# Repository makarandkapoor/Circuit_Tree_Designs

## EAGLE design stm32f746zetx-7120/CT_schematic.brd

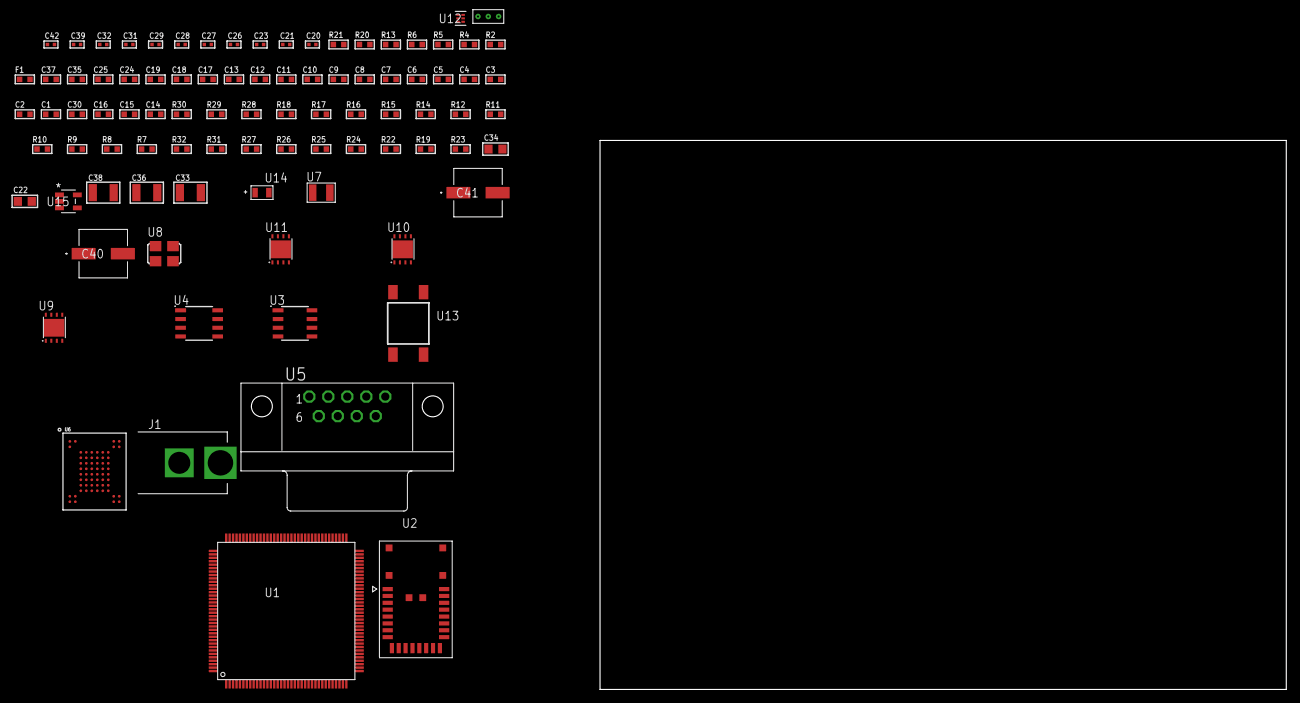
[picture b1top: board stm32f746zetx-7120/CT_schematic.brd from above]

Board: 2 copper layers, 100.0 x 80.0 mm, 90 parts (0 on the bottom side), 58 nets, no tracks yet.

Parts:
C1, C18, C24, C25: 1e-06; C0603
C2, C3, C4, C5, C6, C7, C8, C9, C10, C11, C12, C13, C19: 1e-07; C0603
C14: 4.7e-06; C0603
C15, C16, C30: 2.2e-06; C0603
C17: 1e-08; C0603
C20, C21: 1e-11; C0402
C22, C34: 1e-05; C0805
C23, C31, C32, C42: 1e-08; C0402
C26, C27, C28, C29, C39: 1e-07; C0402
C33, C36, C38: 1e-05; C1210
C35, C37: 8e-07; R0603
C40, C41: 0.0001; EXV-9H
F1: 240.0; L0603
J1: PJ-037B; PJ-037B_PACKAGE
R2, R21: 1000.0; R0603
R4: 4700.0; R0603
R5, R6: 2200.0; R0603
R7, R8, R9, R10, R11, R12, R14, R15, R16, R17, R18, R28, R29: 10000.0; R0603
R13: 120.0; R0603
R19, R22, R24, R25, R27: 100000.0; R0603
R20: 806.0; R0603
R23: 153694.38; R0603
R26, R31: 300000.0; R0603
R30: 82000.0; R0603
R32: 120000.0; R0603
U1: STM32F746ZET6; LQFP144
U2: A2500R24A00GM
U3: AT24C02D-SSHM-T; AT24C02D
U4: MCP2562-E/SN; SOIC-8
U5: 182-009-113R531; 182-009-MALE
U6: mt29f4g08abbdah4; VFBGA-63
U7: ABS07-32.768KHZ-7-T
U8: ASFL1-25MHZ-NCS; ASFL1
U9: LP3878SDX-ADJ/NOPB; WSON-8
U10, U11: LP2951ACSDX/NOPB; WSON-8
U12: TPS3895ADRYR; SON-6
U13: 4-1437565-2; SW_4-1437565-2
U14: Q65110A2395; LGM67K-G1J2-24-Z
U15: nc7sz125m5x; NC7SZ125M5X
U16: Dummy; DUMMY_PACKAGE_199

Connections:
CLK_CRYSTAL_U1_8: C20.1, U1.8, U7.1
CLK_CRYSTAL_U1_9: C21.1, U1.9, U7.2
CLK_U1_23: U1.23, U8.3
GND: C1.2, C2.2, C3.2, C4.2, C5.2, C6.2, C7.2, C8.2, C9.2, C10.2, C11.2, C12.2, C13.2, C14.2, C15.2, C16.2, C17.2, C18.2, C19.2, C20.2, C21.2, C22.2, C23.2, C24.2, C25.2, C26.2, C27.2, C28.2, C29.2, C30.2, C31.2, C32.2, C33.2, C34.2, C35.2, C36.2, C37.2, C38.2, C39.2, C40.2, C41.2, C42.2, J1.2, R2.2, R7.2, R9.2, R11.2, R12.2, R21.2, R24.2, R27.2, R30.2, R32.2, U1.16, U1.31, U1.38, U1.51, U1.61, U1.83, U1.94, U1.107, U1.120, U1.130, U2.8, U2.17, U3.4, U4.2, U4.8, U5.5, U6.C5, U6.F7, U6.K3, U6.K8, U8.2, U9.3, U9.PAD, U10.3, U10.4, U10.PAD, U11.3, U11.4, U11.PAD, U12.2, U14.C, U15.1, U15.3, U16.1
NET_U1_25: R4.1, U1.25, U15.4
NET_U1_33: C17.1, C18.1, F1.1, U1.32, U1.33
NET_U1_71: C15.1, U1.71
NET_U1_106: C16.1, U1.106
NET_U1_136: R5.1, U1.136, U3.6
NET_U1_137: R6.1, U1.137, U3.5
NET_U1_138: R7.1, U1.138
NET_U1_142: U13.3, U13.4
NET_U1_143: R8.1, U1.143
NET_U3_1: R10.1, U3.1
NET_U3_2: R11.1, U3.2
NET_U3_3: R12.1, U3.3
NET_U3_7: R9.1, U3.7
NET_U4_6: R13.2, U4.6
NET_U5_2: R13.2, U4.6, U5.2
NET_U5_3: R13.1, U4.7, U5.3
NET_U6_C3: R18.1, U6.C3
NET_U9_1: C32.1, U9.1
NET_U9_6: R20.2, R21.1, U9.6
NET_U9_8: R19.1, U9.8
NET_U10_5: R22.1, U10.5
NET_U10_7: R23.2, R24.1, U10.7
NET_U11_5: R25.1, U11.5
NET_U11_7: R26.2, R27.1, U11.7
NET_U12_1: R29.1, R30.1, U12.1
NET_U12_3: R31.2, R32.1, U12.3
NET_U12_4: R28.1, U12.4, U15.2
NET_U13_1: R2.1, U13.1, U13.2
PROC_CAN1_RX: U1.103, U4.4
PROC_CAN1_TX: U1.104, U4.1
PROC_FMC_A16: U1.80, U6.D5
PROC_FMC_A17: U1.81, U6.C4
PROC_FMC_D0: U1.85, U6.H4
PROC_FMC_D1: U1.86, U6.J4
PROC_FMC_D2: U1.114, U6.K4
PROC_FMC_D3: U1.115, U6.K5
PROC_FMC_D4: U1.58, U6.K6
PROC_FMC_D5: U1.59, U6.J7
PROC_FMC_D6: U1.60, U6.K7
PROC_FMC_D7: U1.63, U6.J8
PROC_FMC_INT: R14.1, U1.92, U6.C8
PROC_FMC_NCE: R15.1, U1.124, U6.C6
PROC_FMC_NOE: R17.1, U1.118, U6.D4
PROC_FMC_NWE: R16.1, U1.119, U6.C7
PROC_SPI1_MISO: U1.42, U2.10
PROC_SPI1_MOSI: U1.43, U2.11
PROC_SPI1_NSS: U1.40, U2.12
PROC_SPI1_SCK: U1.41, U2.9
PROC_TIM1_CH2: U1.64, U16.2
PROC_TIM1_CH4: U1.67, U16.3
VCC_S1_14V9: C33.1, C35.1, C37.1, C40.1, C41.1, J1.1, R19.2, U9.4, U10.8, U11.8
VCC_TIER1_1V8: C1.1, C2.1, C3.1, C4.1, C5.1, C6.1, C7.1, C8.1, C9.1, C10.1, C11.1, C12.1, C13.1, C14.1, C22.1, C23.1, C25.1, C26.1, C27.1, C28.1, C29.1, C30.1, C34.1, C39.1, C42.1, F1.2, R4.2, R5.2, R6.2, R8.2, R10.2, R14.2, R15.2, R16.2, R17.2, R18.2, R20.1, R28.2, R29.2, R31.1, U1.6, U1.17, U1.30, U1.39, U1.52, U1.62, U1.72, U1.84, U1.108, U1.121, U1.131, U1.144, U2.18, U3.8, U4.5, U6.D3, U6.G4, U6.H8, U6.J6, U9.5, U12.6, U15.5
VCC_TIER1_3V3: C19.1, C31.1, C36.1, R22.2, R23.1, U1.95, U8.4, U10.1
VCC_TIER1_5V0: C24.1, C38.1, R25.2, R26.1, U4.3, U11.1

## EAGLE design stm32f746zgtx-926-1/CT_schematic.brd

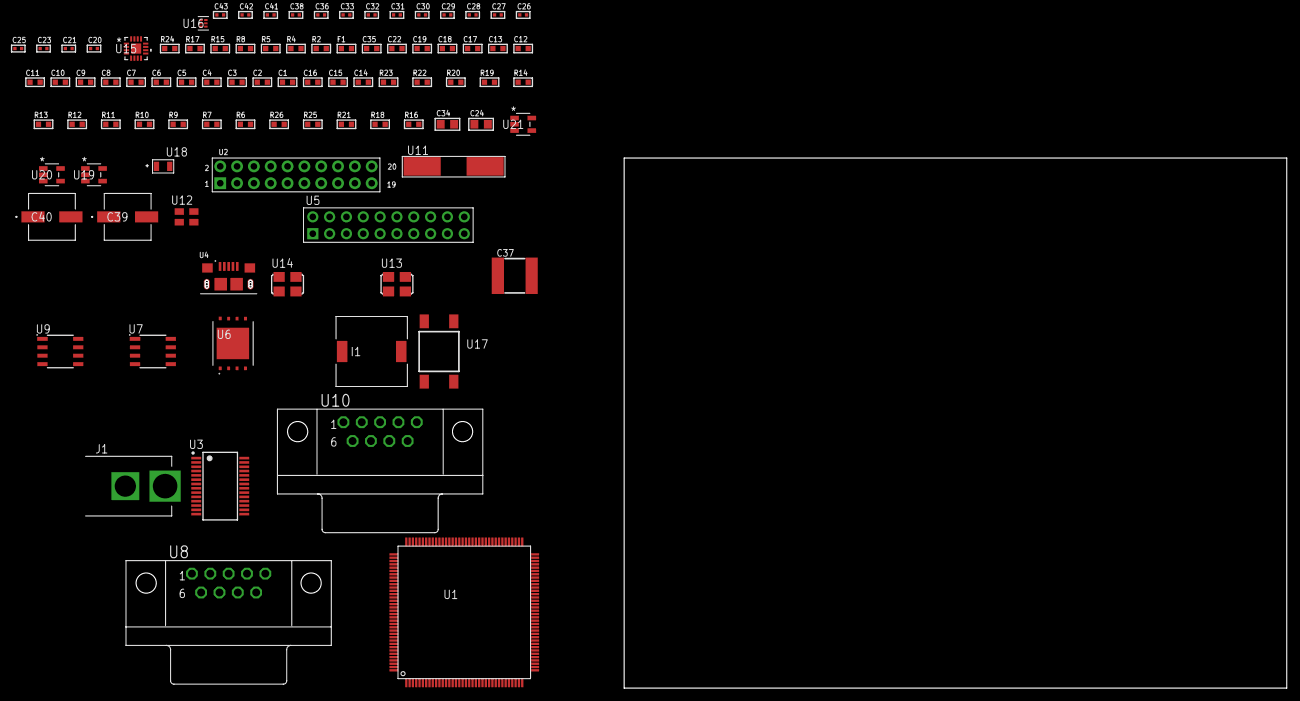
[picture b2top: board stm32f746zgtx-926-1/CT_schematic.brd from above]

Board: 2 copper layers, 91 parts (0 on the bottom side), 67 nets, no tracks yet.

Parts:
C1, C18, C22, C35: 1e-06; C0603
C2, C3, C4, C5, C6, C7, C8, C9, C10, C11, C12, C13, C19: 1e-07; C0603
C14: 4.7e-06; C0603
C15, C16: 2.2e-06; C0603
C17: 1e-08; C0603
C20, C21: 1e-11; C0402
C23, C25, C26, C27, C29, C30, C36, C38: 1e-07; C0402
C24: 4.7e-06; C0805
C28, C31, C32, C33, C41, C42, C43: 1e-08; C0402
C34: 1e-05; C0805
C37: 6.8e-05; 2220
C39, C40: 0.0001; EXV-9H
F1: 240.0; L0603
I1: 3.8e-06; DR1040
J1: PJ-037B; PJ-037B_PACKAGE
R2: 1000.0; R0603
R4, R5, R8: 4700.0; R0603
R6, R7, R9, R10, R11, R12, R13, R14, R22, R23: 10000.0; R0603
R15, R17: 120.0; R0603
R16: 100000.0; R0603
R18: 470000.0; R0603
R19: 20000.0; R0603
R20: 91000.0; R0603
R21: 300000.0; R0603
R24: 9100.0; R0603
R25: 680000.0; R0603
R26: 120000.0; R0603
U1: STM32F746ZGT6; LQFP144
U2: arducam_ov2640; ARDUCAM
U3: FT232RL-REEL; SSOP-28
U4: 10118193-0001LF; FCI_10118193-0001LF
U5: TST-110-05-T-D-RA
U6: S25FL128SDPNFI001; WNG008
U7, U9: SN65HVD230D; SOIC-8
U8, U10: 182-009-113R531; 182-009-MALE
U11: ABLS-25.000MHZ-B2F-T
U12: ASEK-32.768KHz-ECST; ASEK
U13: ASFL1-12MHZ-NCS; ASFL1
U14: ASFL1-25MHZ-NCS; ASFL1
U15: LTC3601EUD#PBF; QFN-16_EP
U16: TPS3895ADRYR; SON-6
U17: 4-1437565-2; SW_4-1437565-2
U18: Q65110A2395; LGM67K-G1J2-24-Z
U19, U20, U21: nc7sz125m5x; NC7SZ125M5X

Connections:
CLK_CRYSTAL_U1_23: C20.1, U1.23, U11.1
CLK_CRYSTAL_U1_24: C21.1, U1.24, U11.2
CLK_U1_8: U1.8, U12.3
CLK_U2_8: U2.8, U14.3
CLK_U3_27: U3.27, U13.3
GND: C1.2, C2.2, C3.2, C4.2, C5.2, C6.2, C7.2, C8.2, C9.2, C10.2, C11.2, C12.2, C13.2, C14.2, C15.2, C16.2, C17.2, C18.2, C19.2, C20.2, C21.2, C22.2, C23.2, C24.2, C25.2, C26.2, C27.2, C28.2, C29.2, C30.2, C31.2, C32.2, C33.2, C34.2, C35.2, C37.1, C37.2, C38.2, C39.2, C40.2, C41.2, C42.2, C43.2, J1.2, R2.2, R6.2, R10.2, R16.2, R18.2, R19.2, R21.2, R24.2, R26.2, U1.16, U1.31, U1.38, U1.51, U1.61, U1.83, U1.94, U1.107, U1.120, U1.130, U2.2, U2.20, U3.7, U3.18, U3.21, U3.25, U3.26, U4.5, U4.6, U4.7, U4.8, U4.9, U5.4, U5.6, U5.8, U5.10, U5.12, U5.14, U5.16, U5.18, U5.20, U6.4, U6.PAD, U7.2, U8.5, U9.2, U10.5, U12.2, U13.2, U14.2, U15.1, U15.9, U15.17, U16.2, U18.C, U19.2, U19.3, U20.1, U20.3, U21.1, U21.3
NET_U1_25: R4.1, U1.25, U20.4
NET_U1_33: C17.1, C18.1, F1.1, U1.32, U1.33
NET_U1_71: C15.1, U1.71
NET_U1_106: C16.1, U1.106
NET_U1_138: R6.1, U1.138
NET_U1_142: U17.3, U17.4
NET_U1_143: R7.1, U1.143
NET_U2_19: R5.1, U2.19, U21.4
NET_U3_14: R9.1, U3.14
NET_U3_17: C25.1, U3.17
NET_U3_19: R10.1, U3.19
NET_U4_1: R8.1, U4.1
NET_U4_2: U3.16, U4.2
NET_U4_3: U3.15, U4.3
NET_U6_3: R12.1, U6.3
NET_U6_7: R14.1, U6.7
NET_U7_6: R15.2, U7.6
NET_U7_8: R16.1, U7.8
NET_U8_2: R15.2, U7.6, U8.2
NET_U8_3: R15.1, U7.7, U8.3
NET_U9_6: R17.2, U9.6
NET_U9_8: R18.1, U9.8
NET_U10_2: R17.2, U9.6, U10.2
NET_U10_3: R17.1, U9.7, U10.3
NET_U15_3: C36.2, I1.1, U15.3, U15.4
NET_U15_6: C36.1, U15.6
NET_U15_7: C35.1, U15.7, U15.12
NET_U15_10: R21.1, U15.10
NET_U15_11: R19.1, R20.1, U15.11
NET_U15_ATNET_3: I1.2, R20.2
NET_U16_1: R23.1, R24.1, U16.1
NET_U16_3: R25.2, R26.1, U16.3
NET_U16_4: R22.1, U16.4, U19.4, U20.2, U21.2
NET_U17_1: R2.1, U17.1, U17.2
PROC_CAN1_RX: U1.103, U7.4
PROC_CAN1_TX: U1.104, U7.1
PROC_CAN2_RX: U1.73, U9.4
PROC_CAN2_TX: U1.74, U9.1
PROC_DCMI_D0: U1.96, U2.18
PROC_DCMI_D1: U1.97, U2.17
PROC_DCMI_D2: U1.98, U2.16
PROC_DCMI_D3: U1.99, U2.15
PROC_DCMI_D4: U1.3, U2.14
PROC_DCMI_D5: U1.117, U2.13
PROC_DCMI_D6: U1.4, U2.12
PROC_DCMI_D7: U1.5, U2.11
PROC_DCMI_D8: U1.111, U2.10
PROC_DCMI_D9: U1.113, U2.9
PROC_DCMI_HSYNC: U1.40, U2.6
PROC_DCMI_PIXCLK: U1.42, U2.7
PROC_DCMI_VSYNC: U1.124, U2.5
PROC_SPI2_MISO: U1.28, U6.2
PROC_SPI2_MOSI: U1.27, U6.5
PROC_SPI2_NSS: R13.1, U1.134, U6.1
PROC_SPI2_SCK: U1.69, U6.6
PROC_SYS_JTCK_SWCLK: U1.109, U5.9
PROC_SYS_JTDO_SWO: U1.133, U5.13
PROC_SYS_JTMS_SWDIO: U1.105, U5.7
RST_OUT_U5_SRESET_B: R11.1, U5.15, U19.1
VCC_S1_9V0: C34.1, C39.1, C40.1, J1.1, U15.15, U15.16
VCC_TIER1_3V3: C1.1, C2.1, C3.1, C4.1, C5.1, C6.1, C7.1, C8.1, C9.1, C10.1, C11.1, C12.1, C13.1, C14.1, C19.1, C22.1, C23.1, C24.1, C26.1, C27.1, C28.1, C29.1, C30.1, C31.1, C32.1, C33.1, C37.2, C38.1, C41.1, C42.1, C43.1, F1.2, I1.2, R4.2, R5.2, R7.2, R9.2, R11.2, R12.2, R13.2, R14.2, R20.2, R22.2, R23.2, R25.1, U1.6, U1.17, U1.30, U1.39, U1.52, U1.62, U1.72, U1.84, U1.95, U1.108, U1.121, U1.131, U1.144, U2.1, U3.4, U3.20, U5.1, U6.8, U7.3, U9.3, U12.4, U13.4, U14.4, U15.8, U16.6, U19.5, U20.5, U21.5

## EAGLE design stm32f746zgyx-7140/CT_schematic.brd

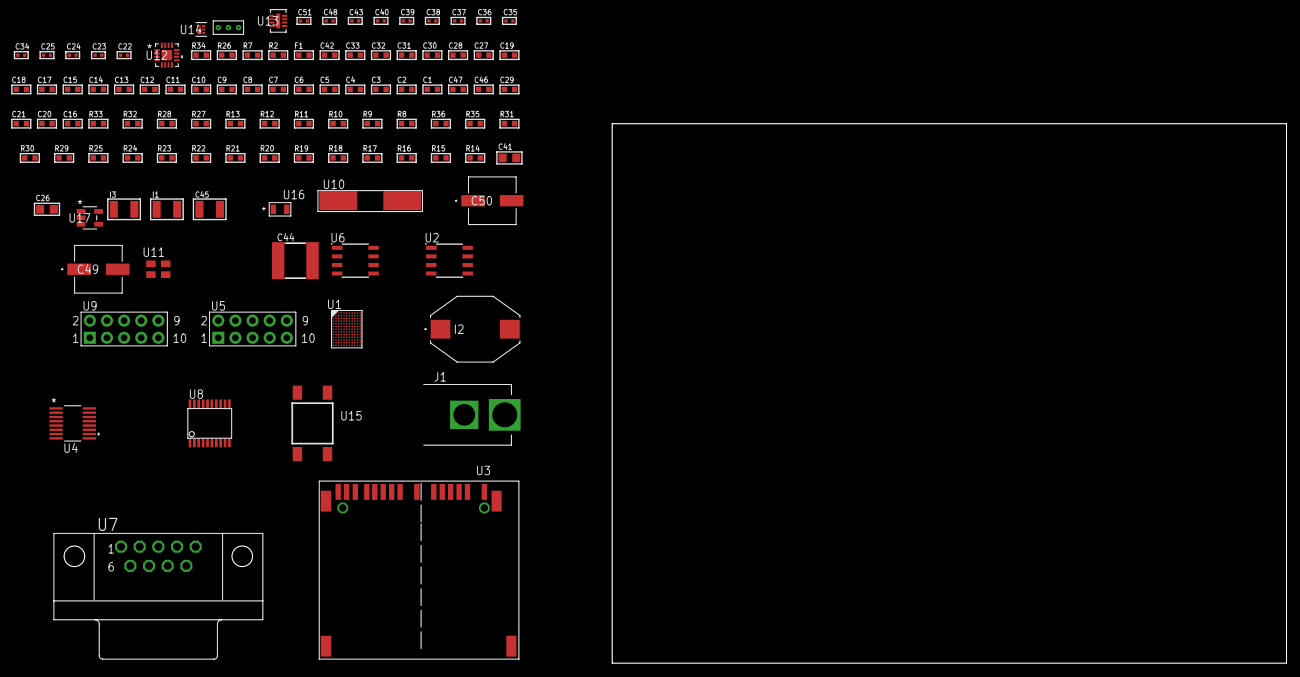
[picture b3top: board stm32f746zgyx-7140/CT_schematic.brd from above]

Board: 2 copper layers, 100.0 x 80.0 mm, 105 parts (0 on the bottom side), 81 nets, no tracks yet.

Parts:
C1, C18, C27, C28, C30, C31, C32, C33, C42: 1e-06; C0603
C2, C3, C4, C5, C6, C7, C8, C9, C10, C11, C12, C13, C14, C15, C19: 1e-07; C0603
C16: 4.7e-06; C0603
C17: 1e-08; C0603
C20, C21, C46: 2.2e-06; C0603
C22, C23: 1e-11; C0402
C24, C40, C51: 1e-08; C0402
C25, C34, C35, C36, C37, C38, C39, C43, C48: 1e-07; C0402
C26, C41: 1e-05; C0805
C29, C47: 2.2e-07; C0603
C44: 6.8e-05; 2220
C45: 1e-05; C1210
C49, C50: 0.0001; EXV-9H
F1: 240.0; L0603
I1, I3: 1e-05; L1210
I2: 1.5e-06; IND_PM3316
J1: PJ-037B; PJ-037B_PACKAGE
R2: 1000.0; R0603
R7: 4700.0; R0603
R8, R9, R10, R11, R12, R13, R32, R33: 10000.0; R0603
R14, R15, R16, R17, R18, R19, R20, R21, R22, R23, R24, R25, R30: 100000.0; R0603
R26: 120.0; R0603
R27: 20000.0; R0603
R28: 91000.0; R0603
R29: 300000.0; R0603
R31: 560000.0; R0603
R34: 9100.0; R0603
R35: 680000.0; R0603
R36: 120000.0; R0603
U1: STM32F746ZGY6; WLCSP143
U2: AT25128B-SSHL-T; SOIC-8
U3: 10100565
U4: LTC2804CGN-1#PBF; SSOP-16
U5, U9: HTSS-105-01-G-D
U6: MCP2562-E/SN; SOIC-8
U7: 182-009-113R531; 182-009-MALE
U8: SP3203ECY-L/TR; TSSOP20-I
U10: ABLS-25.000MHZ-B2F-T
U11: ASEK-32.768KHz-ECST; ASEK
U12: LTC3601EUD#PBF; QFN-16_EP
U13: LT3494AEDDB#TRMPBF; DFN-8_DDB
U14: TPS3895ADRYR; SON-6
U15: 4-1437565-2; SW_4-1437565-2
U16: Q65110A2395; LGM67K-G1J2-24-Z
U17: nc7sz125m5x; NC7SZ125M5X
U18: Dummy; DUMMY_PACKAGE_222

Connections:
CLK_CRYSTAL_U1_H10: C22.1, U1.H10, U10.1
CLK_CRYSTAL_U1_J11: C23.1, U1.J11, U10.2
CLK_U1_D11: U1.D11, U11.3
GND: C1.2, C2.2, C3.2, C4.2, C5.2, C6.2, C7.2, C8.2, C9.2, C10.2, C11.2, C12.2, C13.2, C14.2, C15.2, C16.2, C17.2, C18.2, C19.2, C20.2, C21.2, C22.2, C23.2, C24.2, C25.2, C26.2, C27.2, C28.2, C30.2, C31.2, C32.2, C33.2, C34.2, C35.2, C38.2, C39.2, C40.2, C41.2, C42.2, C44.1, C44.2, C45.2, C46.2, C47.2, C48.2, C49.2, C50.2, C51.2, J1.2, R2.2, R8.2, R10.2, R27.2, R29.2, R34.2, R36.2, U1.D2, U1.E7, U1.F5, U1.H2, U1.H3, U1.H7, U1.K10, U2.4, U3.6, U3.10, U3.12, U3.16, U3.17, U3.20, U3.21, U4.8, U5.9, U6.2, U6.8, U7.5, U8.18, U9.9, U11.2, U12.1, U12.9, U12.17, U13.2, U13.9, U14.2, U16.C, U17.1, U17.3, U18.1
NET_U1_A11: R9.1, U1.A11
NET_U1_C9: R8.1, U1.C9
NET_U1_D1: C21.1, U1.D1
NET_U1_H9: R7.1, U1.H9, U17.4
NET_U1_L10: C17.1, C18.1, F1.1, U1.L10, U1.L11
NET_U1_N2: C20.1, U1.N2
NET_U1_N10: U15.3, U15.4
NET_U1_N11: R10.1, U1.N11
NET_U2_3: R11.1, U2.3
NET_U2_7: R13.1, U2.7
NET_U3_1: R16.1, U3.1
NET_U3_2: R15.1, U3.2
NET_U3_18: U3.18, U3.19
NET_U4_6: C27.1, U4.6
NET_U4_7: C29.1, I1.2, U4.7
NET_U4_9: C28.1, U4.9
NET_U4_10: C29.2, U4.10
NET_U4_11: R25.1, U4.11
NET_U5_3: U4.1, U5.3
NET_U5_4: U4.2, U5.4
NET_U5_5: U4.3, U5.5
NET_U5_6: U4.4, U5.6
NET_U6_6: R26.2, U6.6
NET_U7_2: R26.2, U6.6, U7.2
NET_U7_3: R26.1, U6.7, U7.3
NET_U8_1: C36.1, U8.1
NET_U8_2: C38.1, U8.2
NET_U8_3: C36.2, U8.3
NET_U8_4: C37.1, U8.4
NET_U8_5: C37.2, U8.5
NET_U8_6: C39.1, U8.6
NET_U9_3: U8.14, U9.3
NET_U9_4: U8.13, U9.4
NET_U9_5: U8.17, U9.5
NET_U9_6: U8.16, U9.6
NET_U12_3: C43.2, I2.1, U12.3, U12.4
NET_U12_6: C43.1, U12.6
NET_U12_7: C42.1, U12.7, U12.12
NET_U12_10: R29.1, U12.10
NET_U12_11: R27.1, R28.1, U12.11
NET_U12_ATNET_3: I2.2, R28.2
NET_U13_1: I3.1, U13.1
NET_U13_5: R30.1, U13.5
NET_U13_6: R31.1, U13.6
NET_U13_8: C47.1, U13.8
NET_U14_1: R33.1, R34.1, U14.1
NET_U14_3: R35.2, R36.1, U14.3
NET_U14_4: R32.1, U14.4, U17.2
NET_U15_1: R2.1, U15.1, U15.2
PROC_ADC1_IN3: U1.M11, U18.2
PROC_ADC1_IN5: U1.M9, U18.3
PROC_CAN1_RX: U1.B3, U6.4
PROC_CAN1_TX: U1.C4, U6.1
PROC_SDMMC1_CK: R14.1, U1.C3, U3.8
PROC_SDMMC1_D0: R17.1, U1.E4, U3.4
PROC_SDMMC1_D1: R18.1, U1.E3, U3.3
PROC_SDMMC1_D2: R19.1, U1.A2, U3.15
PROC_SDMMC1_D3: R20.1, U1.B2, U3.14
PROC_SDMMC1_D4: R21.1, U1.A9, U3.13
PROC_SDMMC1_D5: R22.1, U1.B9, U3.11
PROC_SDMMC1_D6: R23.1, U1.F2, U3.7
PROC_SDMMC1_D7: R24.1, U1.F3, U3.5
PROC_SPI1_MISO: U1.C7, U2.2
PROC_SPI1_MOSI: U1.C8, U2.5
PROC_SPI1_NSS: R12.1, U1.M10, U2.1
PROC_SPI1_SCK: U1.B7, U2.6
PROC_UART4_CTS: U1.N8, U4.13
PROC_UART4_RTS: U1.C2, U4.15
PROC_UART4_RX: U1.K8, U4.16
PROC_UART4_TX: U1.K9, U4.14
PROC_UART7_CTS: U1.G8, U8.8
PROC_UART7_RTS: U1.H11, U8.10
PROC_UART7_RX: U1.G10, U8.11
PROC_UART7_TX: U1.F7, U8.7
VCC_S1_4V6: C41.1, C45.1, C49.1, C50.1, I3.2, J1.1, R30.2, U12.15, U12.16, U13.3, U13.4
VCC_TIER1_3V3: C1.1, C2.1, C3.1, C4.1, C5.1, C6.1, C7.1, C8.1, C9.1, C10.1, C11.1, C12.1, C13.1, C14.1, C15.1, C16.1, C19.1, C24.1, C25.1, C26.1, C30.1, C31.1, C33.1, C34.1, C35.1, C40.1, C44.2, C48.1, C51.1, F1.2, I1.1, I2.2, R7.2, R9.2, R11.2, R12.2, R13.2, R14.2, R15.2, R16.2, R17.2, R18.2, R19.2, R20.2, R21.2, R22.2, R23.2, R24.2, R25.2, R28.2, R32.2, R33.2, R35.1, U1.A1, U1.C1, U1.C5, U1.C11, U1.D7, U1.E6, U1.E10, U1.G1, U1.G7, U1.J5, U1.J6, U1.J7, U1.J8, U1.L1, U2.8, U3.9, U4.5, U4.12, U6.5, U8.12, U8.19, U11.4, U12.8, U14.6, U17.5
VCC_TIER1_5V0: C32.1, C46.1, R31.2, U6.3, U13.7

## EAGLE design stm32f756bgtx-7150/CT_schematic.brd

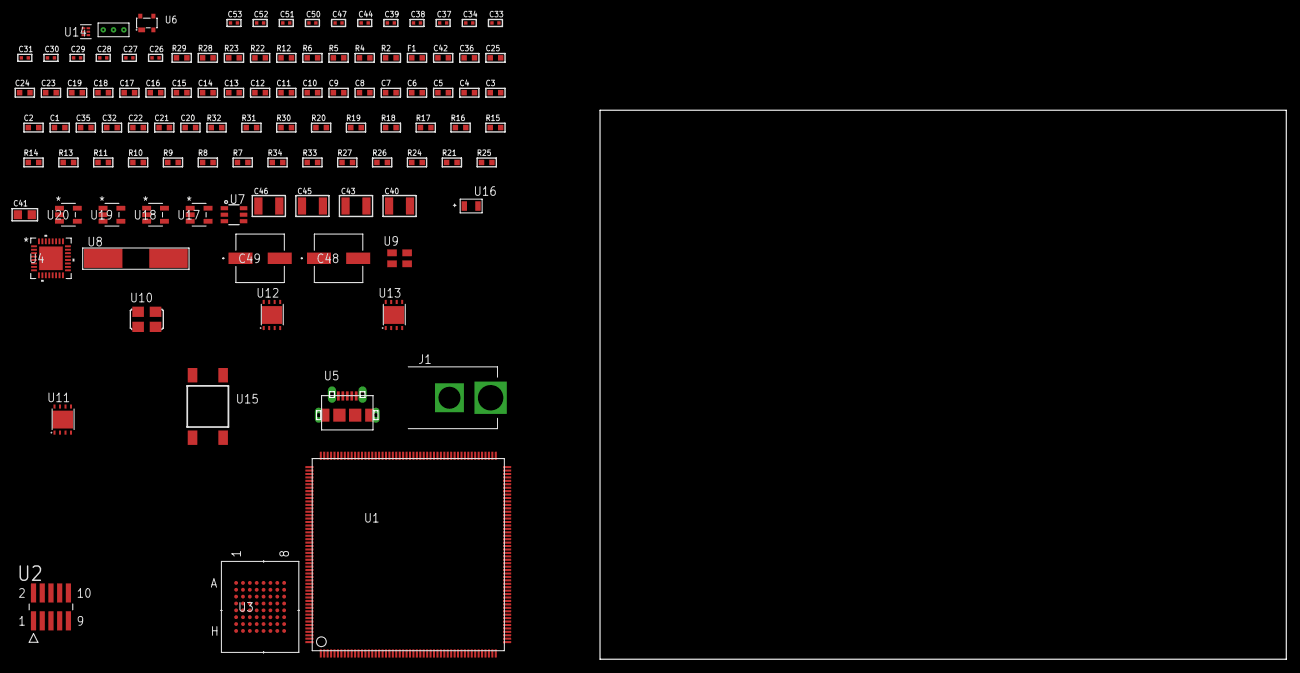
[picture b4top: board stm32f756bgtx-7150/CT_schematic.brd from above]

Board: 2 copper layers, 108 parts (0 on the bottom side), 105 nets, no tracks yet.

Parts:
C1, C24, C36: 1e-06; C0603
C2, C3, C4, C5, C6, C7, C8, C9, C10, C11, C12, C13, C14, C15, C16, C17, C18, C19, C25: 1e-07; C0603
C20: 4.7e-06; C0603
C21, C22, C32, C35: 2.2e-06; C0603
C23: 1e-08; C0603
C26, C27: 1e-11; C0402
C28, C31, C33, C34, C47: 1e-07; C0402
C29, C30, C37, C38, C39, C44, C50, C51, C52, C53: 1e-08; C0402
C40, C43, C45, C46: 1e-05; C1210
C41: 1e-05; C0805
C42: 8e-07; R0603
C48, C49: 0.0001; EXV-9H
F1: 240.0; L0603
J1: PJ-037B; PJ-037B_PACKAGE
R2, R23, R29: 1000.0; R0603
R4, R5, R6: 4700.0; R0603
R7, R8, R9, R10, R11, R13, R14, R15, R16, R17, R19, R20, R30, R31: 10000.0; R0603
R12: 5.0; R0603
R18: 47000.0; R0603
R21, R24, R26, R27: 100000.0; R0603
R22: 806.0; R0603
R25: 153694.38; R0603
R28: 3900.0; R0603
R32: 82000.0; R0603
R33: 300000.0; R0603
R34: 120000.0; R0603
U1: STM32F756BGT6; LQFP208
U2: FTSH-105-01-L-DV-K; SAMTEC_FTSH-105-01-L-DV-K
U3: mt28ew256aba1HPC-0SIT; LBGA-64
U4: TUSB1210BRHBR; RHB32_3P45X3P45
U5: 47590-0001; MICRO_USB_AB
U6: prtr5v0u2ax; SOT143B
U7: MAX4995AAUT+T; SOT-23-6
U8: ABLS-25.000MHZ-B2F-T
U9: ASEK-32.768KHz-ECST; ASEK
U10: ASFL1-19.2MHZ-NCS; ASFL1
U11, U13: LP3878SDX-ADJ/NOPB; WSON-8
U12: LP2951ACSDX/NOPB; WSON-8
U14: TPS3895ADRYR; SON-6
U15: 4-1437565-2; SW_4-1437565-2
U16: Q65110A2395; LGM67K-G1J2-24-Z
U17, U18, U19, U20: nc7sz125m5x; NC7SZ125M5X
U21: Dummy; DUMMY_PACKAGE_239

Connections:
CLK_CRYSTAL_U1_32: C26.1, U1.32, U8.1
CLK_CRYSTAL_U1_33: C27.1, U1.33, U8.2
CLK_U1_9: U1.9, U9.3
CLK_U4_1: U4.1, U10.3
GND: C1.2, C2.2, C3.2, C4.2, C5.2, C6.2, C7.2, C8.2, C9.2, C10.2, C11.2, C12.2, C13.2, C14.2, C15.2, C16.2, C17.2, C18.2, C19.2, C20.2, C21.2, C22.2, C23.2, C24.2, C25.2, C26.2, C27.2, C28.2, C29.2, C30.2, C31.2, C32.2, C33.2, C34.2, C35.2, C36.2, C37.2, C38.2, C39.2, C40.2, C41.2, C42.2, C43.2, C44.2, C45.2, C46.2, C47.2, C48.2, C49.2, C50.2, C51.2, C52.2, C53.2, J1.2, R2.2, R7.2, R12.2, R18.2, R20.2, R23.2, R26.2, R29.2, R32.2, R34.2, U1.14, U1.25, U1.40, U1.51, U1.60, U1.72, U1.82, U1.93, U1.114, U1.125, U1.136, U1.149, U1.170, U1.184, U1.202, U2.3, U2.5, U3.E8, U3.H2, U3.H7, U4.33, U5.5, U5.6, U5.7, U5.8, U5.9, U6.1, U7.2, U9.2, U10.2, U11.3, U11.PAD, U12.3, U12.4, U12.PAD, U13.3, U13.PAD, U14.2, U16.C, U17.2, U17.3, U18.1, U18.3, U19.1, U19.3, U20.1, U20.3, U21.1
NET_U1_34: R5.1, U1.34, U19.4
NET_U1_42: C23.1, C24.1, F1.1, U1.41, U1.42
NET_U1_92: C21.1, U1.92
NET_U1_148: C22.1, U1.148
NET_U1_197: R7.1, U1.197
NET_U1_203: R8.1, U1.203
NET_U1_208: U15.3, U15.4
NET_U2_9: R12.1, U2.9
NET_U3_B4: R16.1, U3.B4
NET_U3_B5: R4.1, U3.B5, U18.4
NET_U4_11: R19.1, U4.11
NET_U4_12: C35.1, U4.12
NET_U4_14: R20.1, U4.14
NET_U4_20: C32.1, U4.20
NET_U4_27: R6.1, U4.27, U20.4
NET_U5_1: C36.1, U4.22, U5.1, U6.4, U7.1
NET_U5_2: U4.19, U5.2, U6.3
NET_U5_3: U4.18, U5.3, U6.2
NET_U5_4: U4.23, U5.4
NET_U7_3: R18.1, U7.3
NET_U7_4: U4.17, U7.4
NET_U11_1: C39.1, U11.1
NET_U11_6: R22.2, R23.1, U11.6
NET_U11_8: R21.1, U11.8
NET_U12_5: R24.1, U12.5
NET_U12_7: R25.2, R26.1, U12.7
NET_U13_1: C44.1, U13.1
NET_U13_6: R28.2, R29.1, U13.6
NET_U13_8: R27.1, U13.8
NET_U14_1: R31.1, R32.1, U14.1
NET_U14_3: R33.2, R34.1, U14.3
NET_U14_4: R30.1, U14.4, U17.4, U18.2, U19.2, U20.2
NET_U15_1: R2.1, U15.1, U15.2
PROC_FMC_A0: U1.16, U3.E2
PROC_FMC_A1: U1.17, U3.D2
PROC_FMC_A2: U1.18, U3.C2
PROC_FMC_A3: U1.22, U3.A2
PROC_FMC_A4: U1.23, U3.B2
PROC_FMC_A5: U1.24, U3.D3
PROC_FMC_A6: U1.71, U3.C3
PROC_FMC_A7: U1.74, U3.A3
PROC_FMC_A8: U1.75, U3.B6
PROC_FMC_A9: U1.76, U3.A6
PROC_FMC_A10: U1.77, U3.C6
PROC_FMC_A11: U1.78, U3.D6
PROC_FMC_A12: U1.129, U3.B7
PROC_FMC_A13: U1.130, U3.A7
PROC_FMC_A14: U1.131, U3.C7
PROC_FMC_A15: U1.132, U3.D7
PROC_FMC_A16: U1.111, U3.E7
PROC_FMC_A17: U1.112, U3.B3
PROC_FMC_A18: U1.113, U3.C4
PROC_FMC_A19: U1.2, U3.D5
PROC_FMC_A20: U1.3, U3.D4
PROC_FMC_A21: U1.4, U3.C5
PROC_FMC_A22: U1.5, U3.B8
PROC_FMC_A23: U1.1, U3.C8
PROC_FMC_D0: U1.116, U3.E3
PROC_FMC_D1: U1.117, U3.H3
PROC_FMC_D2: U1.164, U3.E4
PROC_FMC_D3: U1.165, U3.H4
PROC_FMC_D4: U1.79, U3.H5
PROC_FMC_D5: U1.80, U3.E5
PROC_FMC_D6: U1.81, U3.H6
PROC_FMC_D7: U1.84, U3.E6
PROC_FMC_D8: U1.85, U3.F3
PROC_FMC_D9: U1.86, U3.G3
PROC_FMC_D10: U1.87, U3.F4
PROC_FMC_D11: U1.88, U3.G4
PROC_FMC_D12: U1.89, U3.F5
PROC_FMC_D13: U1.108, U3.G6
PROC_FMC_D14: U1.109, U3.F6
PROC_FMC_D15: U1.110, U3.G7
PROC_FMC_NBL0: R17.1, U1.200, U3.F7
PROC_FMC_NE2: R13.1, U1.178, U3.F2
PROC_FMC_NOE: R14.1, U1.168, U3.G2
PROC_FMC_NWAIT: U1.172, U3.A4
PROC_FMC_NWE: R15.1, U1.169, U3.A5
PROC_PC13: U1.8, U21.3
PROC_PI8: U1.7, U21.2
PROC_SYS_JTCK_SWCLK: R10.1, U1.159, U2.4
PROC_SYS_JTDO_SWO: U1.192, U2.6
PROC_SYS_JTMS_SWDIO: R11.1, U1.147, U2.2
PROC_USB_OTG_HS_ULPI_CK: U1.54, U4.26
PROC_USB_OTG_HS_ULPI_D0: U1.50, U4.3
PROC_USB_OTG_HS_ULPI_D1: U1.61, U4.4
PROC_USB_OTG_HS_ULPI_D2: U1.62, U4.5
PROC_USB_OTG_HS_ULPI_D3: U1.90, U4.6
PROC_USB_OTG_HS_ULPI_D4: U1.91, U4.7
PROC_USB_OTG_HS_ULPI_D5: U1.104, U4.9
PROC_USB_OTG_HS_ULPI_D6: U1.105, U4.10
PROC_USB_OTG_HS_ULPI_D7: U1.194, U4.13
PROC_USB_OTG_HS_ULPI_DIR: U1.13, U4.31
PROC_USB_OTG_HS_ULPI_NXT: U1.38, U4.2
PROC_USB_OTG_HS_ULPI_STP: U1.35, U4.29
RST_OUT_U2_JTAG_RST_B: R9.1, U2.10, U17.1
VCC_S1_13V8: C40.1, C42.1, C45.1, C48.1, C49.1, J1.1, R21.2, R27.2, U11.4, U12.8, U13.4
VCC_TIER1_1V8: C1.1, C2.1, C3.1, C4.1, C5.1, C6.1, C7.1, C8.1, C9.1, C10.1, C11.1, C12.1, C13.1, C14.1, C15.1, C16.1, C17.1, C18.1, C19.1, C20.1, C28.1, C29.1, C33.1, C34.1, C41.1, C47.1, C50.1, C51.1, C52.1, C53.1, F1.2, R4.2, R5.2, R6.2, R8.2, R9.2, R10.2, R11.2, R13.2, R14.2, R15.2, R16.2, R17.2, R19.2, R22.1, R30.2, R31.2, R33.1, U1.6, U1.15, U1.26, U1.39, U1.52, U1.59, U1.73, U1.83, U1.94, U1.103, U1.115, U1.124, U1.150, U1.158, U1.171, U1.185, U1.204, U2.1, U3.D8, U3.F1, U4.28, U4.30, U4.32, U11.5, U14.6, U17.5, U18.5, U19.5, U20.5
VCC_TIER1_3V3: C25.1, C30.1, C31.1, C37.1, C38.1, C43.1, R24.2, R25.1, U1.137, U3.G5, U4.21, U9.4, U10.4, U12.1
VCC_TIER1_5V0: C46.1, R28.1, U7.5, U13.5

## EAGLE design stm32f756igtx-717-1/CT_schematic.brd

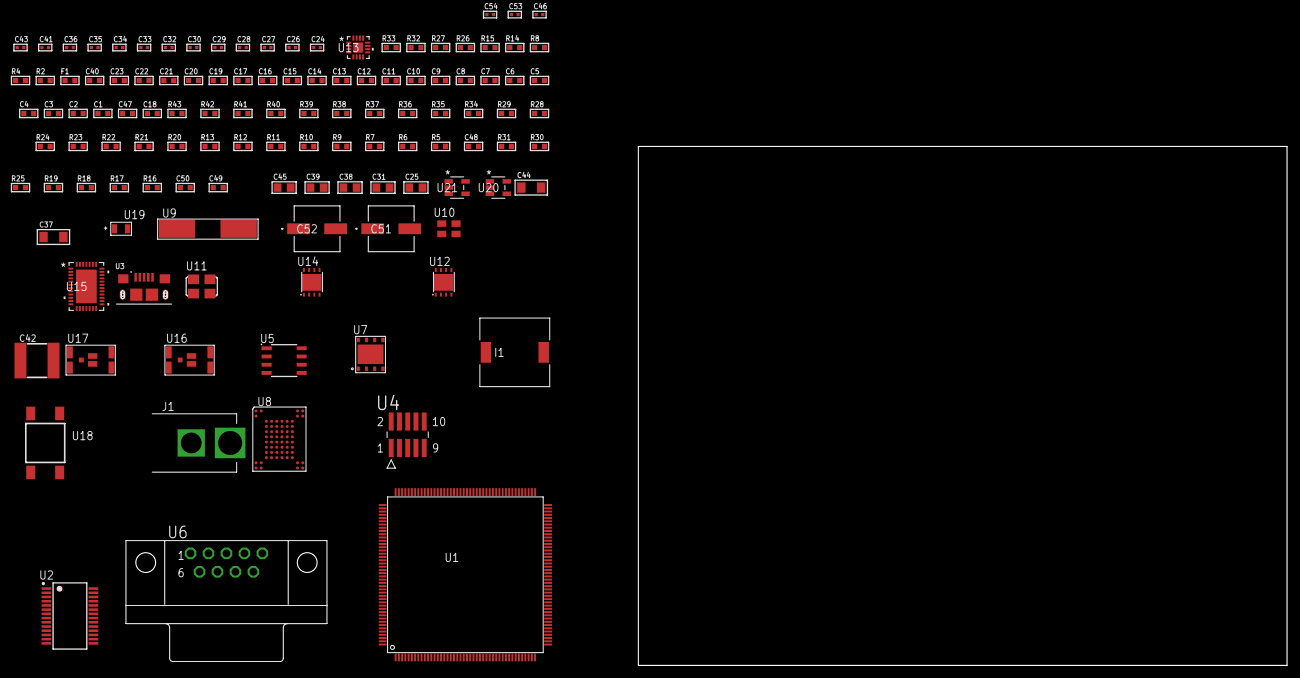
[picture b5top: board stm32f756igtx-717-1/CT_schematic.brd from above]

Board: 2 copper layers, 119 parts (0 on the bottom side), 83 nets, no tracks yet.

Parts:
C1, C20, C40: 1e-06; C0603
C2, C3, C4, C5, C6, C7, C8, C9, C10, C11, C12, C13, C14, C15, C16, C17, C21, C22, C23: 1e-07; C0603
C18: 4.7e-06; C0603
C19: 1e-08; C0603
C24, C26, C27, C28, C29, C30, C32, C33, C41, C46: 1e-07; C0402
C25: 4.7e-06; C0805
C31, C38, C39, C45: 1e-05; C0805
C34, C35, C36, C43, C53, C54: 1e-08; C0402
C37, C44: 1e-05; C1206
C42: 6.8e-05; 2220
C47: 2.2e-06; C0603
C48: 2.45e-08; R0603
C49: 2.8258362168397e-09; R0603
C50: 7.105e-09; R0603
C51, C52: 0.0001; EXV-9H
F1: 240.0; L0603
I1: 5.2e-06; DR1040
J1: PJ-037B; PJ-037B_PACKAGE
R2, R27, R33: 1000.0; R0603
R4, R8: 4700.0; R0603
R5, R6, R7, R9, R10, R11, R12, R13, R20, R21, R22, R23, R24, R34, R36, R37, R40, R41, R42: 10000.0; R0603
R14: 5.0; R0603
R15: 120.0; R0603
R16: 470000.0; R0603
R17, R18, R19, R25, R31: 100000.0; R0603
R26, R32: 200.0; R0603
R28: 20000.0; R0603
R29: 91000.0; R0603
R30: 300000.0; R0603
R35, R43: 75000.0; R0603
R38, R39: 95300.0; R0603
U1: STM32F756IGT6; LQFP176
U2: FT232RL-REEL; SSOP-28
U3: 10118193-0001LF; FCI_10118193-0001LF
U4: FTSH-105-01-L-DV-K; SAMTEC_FTSH-105-01-L-DV-K
U5: SN65HVD230D; SOIC-8
U6: 182-009-113R531; 182-009-MALE
U7: SST26VF064B-104I/MF; WFDN-8
U8: TH58NVG3S0HBAI4
U9: ABLS-12.000MHZ-B4-T
U10: ASEK-32.768KHz-ECST; ASEK
U11: ASFL1-25MHZ-NCS; ASFL1
U12, U14: LP3878SDX-ADJ/NOPB; WSON-8
U13: LTC3601EUD#PBF; QFN-16_EP
U15: LTC2928CUHF#PBF; QFN-38_UHF
U16, U17: IRF8306MTRPbF; IRF8306MTRPBF
U18: 4-1437565-2; SW_4-1437565-2
U19: Q65110A2395; LGM67K-G1J2-24-Z
U20, U21: nc7sz125m5x; NC7SZ125M5X

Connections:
CLK_CRYSTAL_U2_27: U2.27, U9.1
CLK_CRYSTAL_U2_28: U2.28, U9.2
CLK_U1_9: U1.9, U10.3
CLK_U1_29: U1.29, U11.3
GND: C1.2, C2.2, C3.2, C4.2, C5.2, C6.2, C7.2, C8.2, C9.2, C10.2, C11.2, C12.2, C13.2, C14.2, C15.2, C16.2, C17.2, C18.2, C19.2, C20.2, C21.2, C22.2, C23.2, C24.2, C25.2, C26.2, C27.2, C28.2, C29.2, C30.2, C31.2, C32.2, C33.2, C34.2, C35.2, C36.2, C37.2, C38.2, C39.2, C40.2, C42.1, C42.2, C43.2, C44.2, C45.2, C46.2, C47.2, C48.2, C49.2, C50.2, C51.2, C52.2, C53.2, C54.2, J1.2, R2.2, R5.2, R10.2, R14.2, R16.2, R27.2, R28.2, R30.2, R33.2, R35.2, R38.2, R39.2, R40.2, R41.2, R42.2, U1.14, U1.22, U1.37, U1.61, U1.71, U1.90, U1.102, U1.113, U1.126, U1.135, U1.148, U1.158, U2.7, U2.18, U2.21, U2.25, U2.26, U3.5, U3.6, U3.7, U3.8, U3.9, U4.3, U4.5, U5.2, U6.5, U7.4, U7.9, U8.C5, U8.K3, U8.K8, U10.2, U11.2, U12.3, U12.PAD, U13.1, U13.9, U13.17, U14.3, U14.PAD, U15.8, U15.9, U15.10, U15.12, U15.13, U15.24, U15.25, U15.30, U15.32, U15.39, U19.C, U20.2, U20.3, U21.1, U21.3
NET_U1_31: R4.1, U1.31, U21.4
NET_U1_39: C19.1, C20.1, F1.1, U1.38, U1.39
NET_U1_48: R7.1, U1.48
NET_U1_125: C23.1, U1.125
NET_U1_166: R5.1, U1.166
NET_U1_171: R6.1, U1.171
NET_U1_176: U18.3, U18.4
NET_U2_14: R9.1, U2.14
NET_U2_17: C26.1, U2.17
NET_U2_19: R10.1, U2.19
NET_U3_1: R8.1, U3.1
NET_U3_2: U2.16, U3.2
NET_U3_3: U2.15, U3.3
NET_U4_9: R14.1, U4.9
NET_U5_6: R15.2, U5.6
NET_U5_8: R16.1, U5.8
NET_U6_2: R15.2, U5.6, U6.2
NET_U6_3: R15.1, U5.7, U6.3
NET_U8_C3: R23.1, U8.C3
NET_U12_1: C36.1, U12.1
NET_U12_6: R26.2, R27.1, U12.6
NET_U12_8: R25.1, U12.8
NET_U13_3: C41.2, I1.1, U13.3, U13.4
NET_U13_6: C41.1, U13.6
NET_U13_7: C40.1, U13.7, U13.12
NET_U13_10: R30.1, U13.10
NET_U13_11: R28.1, R29.1, U13.11
NET_U13_ATNET_3: I1.2, R29.2
NET_U14_1: C43.1, U14.1
NET_U14_6: R32.2, R33.1, U14.6
NET_U14_8: R31.1, U14.8
NET_U15_3: R41.1, U15.3
NET_U15_6: R38.1, U15.6
NET_U15_7: R39.1, U15.7
NET_U15_16: R40.1, R43.1, U15.16
NET_U15_18: R37.1, U15.18
NET_U15_19: R36.1, U15.19, U15.20
NET_U15_21: R34.1, R35.1, U15.21, U20.4, U21.2
NET_U15_22: C46.1, R34.2, R36.2, R37.2, U15.11, U15.22
NET_U15_26: C49.1, U15.26
NET_U15_27: C48.1, U15.27
NET_U15_28: C50.1, U15.28
NET_U15_38: R42.1, U15.38
NET_U16_3: U15.2, U16.3
NET_U17_3: U15.37, U17.3
NET_U18_1: R2.1, U18.1, U18.2
PROC_CAN1_RX: U1.11, U5.4
PROC_CAN1_TX: U1.123, U5.1
PROC_FMC_A16: U1.99, U8.D5
PROC_FMC_A17: U1.100, U8.C4
PROC_FMC_D0: U1.104, U8.H4
PROC_FMC_D1: U1.105, U8.J4
PROC_FMC_D2: U1.142, U8.K4
PROC_FMC_D3: U1.143, U8.K5
PROC_FMC_D4: U1.68, U8.K6
PROC_FMC_D5: U1.69, U8.J7
PROC_FMC_D6: U1.70, U8.K7
PROC_FMC_D7: U1.73, U8.J8
PROC_FMC_INT: R24.1, U1.111, U8.C8
PROC_FMC_NCE: R20.1, U1.152, U8.C6
PROC_FMC_NOE: R21.1, U1.146, U8.D4
PROC_FMC_NWE: R22.1, U1.147, U8.C7
PROC_QUADSPI_BK1_IO0: U1.26, U7.5
PROC_QUADSPI_BK1_IO1: U1.27, U7.2
PROC_QUADSPI_BK1_IO2: R18.1, U1.1, U7.3
PROC_QUADSPI_BK1_IO3: R19.1, U1.24, U7.7
PROC_QUADSPI_BK1_NCS: R17.1, U1.164, U7.1
PROC_QUADSPI_CLK: U1.58, U7.6
PROC_SYS_JTCK_SWCLK: R12.1, U1.137, U4.4
PROC_SYS_JTDO_SWO: U1.161, U4.6
PROC_SYS_JTMS_SWDIO: R13.1, U1.124, U4.2
RST_OUT_U4_JTAG_RST_B: R11.1, U4.10, U20.1
VCC_9V5: C47.1, C51.1, C52.1, J1.1, R43.2, U15.23, U16.1, U16.2, U16.6, U16.7, U17.1, U17.2, U17.6, U17.7
VCC_S1_9V5: C37.1, C39.1, R25.2, U12.4, U13.15, U13.16, U16.4, U16.5
VCC_S2_9V5: C44.1, R31.2, U14.4, U17.4, U17.5
VCC_TIER1_1V2: C22.1, C38.1, R26.1, U1.81, U12.5
VCC_TIER1_3V3: C1.1, C2.1, C3.1, C4.1, C5.1, C6.1, C7.1, C8.1, C9.1, C10.1, C11.1, C12.1, C13.1, C14.1, C15.1, C16.1, C17.1, C18.1, C21.1, C24.1, C25.1, C27.1, C28.1, C29.1, C30.1, C31.1, C32.1, C33.1, C34.1, C35.1, C42.2, C53.1, C54.1, F1.2, I1.2, R4.2, R6.2, R7.2, R9.2, R11.2, R12.2, R13.2, R17.2, R18.2, R19.2, R20.2, R21.2, R22.2, R23.2, R24.2, R29.2, U1.6, U1.15, U1.23, U1.36, U1.49, U1.62, U1.72, U1.82, U1.91, U1.103, U1.114, U1.127, U1.136, U1.149, U1.159, U1.172, U2.4, U2.20, U4.1, U5.3, U7.8, U8.H8, U8.J6, U10.4, U11.4, U13.8, U20.5, U21.5
VCC_TIER2_1V2: C45.1, R32.1, U14.5
